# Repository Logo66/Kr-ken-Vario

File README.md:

# AURA-Kruecke

ESP32-S3-basiertes Variometer-Prototyping auf dem LilyGo T5 E-Paper S3 Pro.

## Hardware

- **Board:** LilyGo T5 E-Paper S3 Pro (ESP32-S3, 16 MB Flash, OPI PSRAM)
- **Sensoren (extern via I2C):** 2x BMP581, LSM6DSO32, BNO085, SHT40
- **Onboard:** BQ25896 Charger, BQ27220 Fuel Gauge, PCF85063 RTC, 4.7" E-Paper

## Setup

1. [PlatformIO](https://platformio.org/) installieren
2. `pio run` — kompiliert und zieht Dependencies
3. `pio run -t upload` — flasht auf das Board
4. `pio device monitor` — Serial Monitor @ 115200 Baud

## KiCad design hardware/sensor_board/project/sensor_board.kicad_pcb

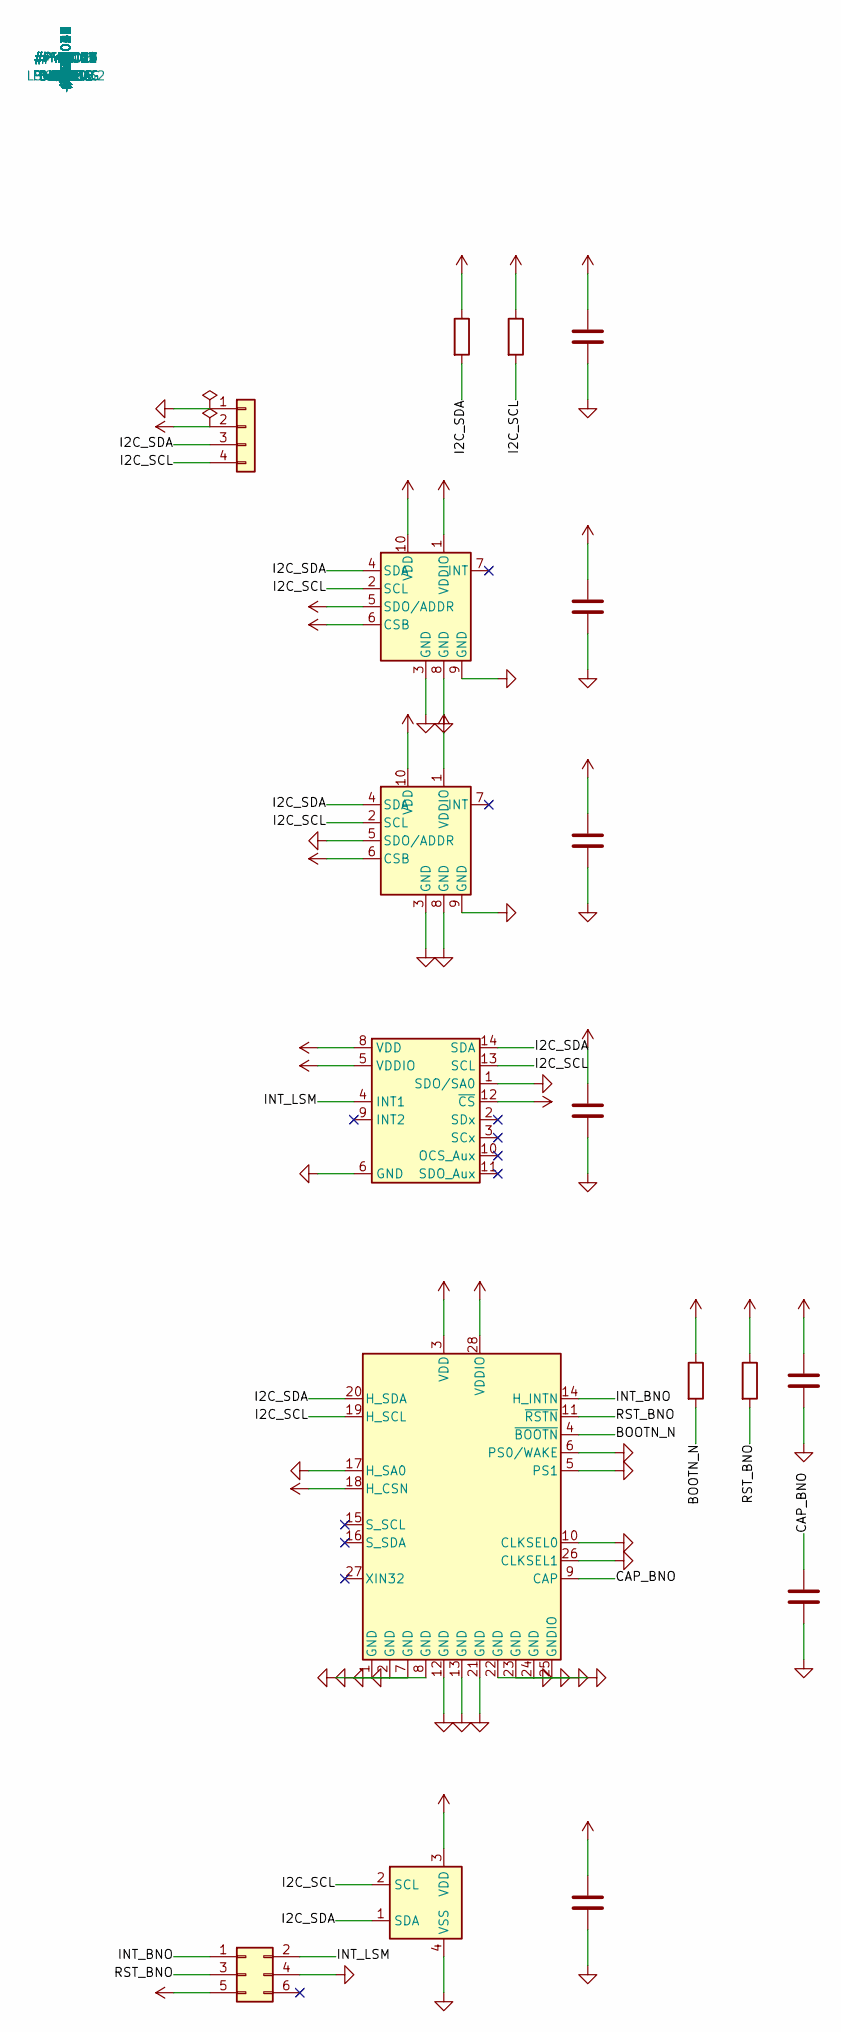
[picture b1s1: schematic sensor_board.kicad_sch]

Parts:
C1, C2, C3, C4, C5, C7: 100n; C_0402_1005Metric
C6: 10u; C_0805_2012Metric
J1: Qwiic; JST_SH_SM04B-SRSS-TB_1x04-1MP_P1.00mm_Horizontal
J2: INT_HDR; PinHeader_2x03_P1.27mm_Vertical
R1, R2: 4.7k; R_0402_1005Metric
R3, R4: 10k; R_0402_1005Metric
U1, U2: BMP581; BMP581_LGA-10_2x2mm
U3: LSM6DSO32; Bosch_LGA-14_3x2.5mm_P0.5mm
U4: BNO085; LGA-28_5.2x3.8mm_P0.5mm
U5: SHT40; Sensirion_DFN-4_1.5x1.5mm_P0.8mm_SHT4x_NoCentralPad

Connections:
+3V3: C1.1, C2.1, C3.1, C4.1, C5.1, C6.1, J1.2, J2.5, R1.1, R2.1, R3.1, R4.1, U1.1 (VDDIO), U1.5 (SDO/ADDR), U1.6 (CSB), U1.10 (VDD), U2.1 (VDDIO), U2.6 (CSB), U2.10 (VDD), U3.5 (VDDIO), U3.8 (VDD), U3.12 (~CS), U4.3 (VDD), U4.18 (H_CSN), U4.28 (VDDIO), U5.3 (VDD)
BOOTN_N: R3.2, U4.4 (~BOOTN)
CAP_BNO: C7.1, U4.9 (CAP)
GND: C1.2, C2.2, C3.2, C4.2, C5.2, C6.2, C7.2, J1.1, J1.MP, J2.4, U1.3 (GND), U1.8 (GND), U1.9 (GND), U2.3 (GND), U2.5 (SDO/ADDR), U2.8 (GND), U2.9 (GND), U3.1 (SDO/SA0), U3.6 (GND), U3.7 (GND), U4.1 (GND), U4.2 (GND), U4.5 (PS1), U4.6 (PS0/WAKE), U4.7 (GND), U4.8 (GND), U4.10 (CLKSEL0), U4.12 (GND), U4.13 (GND), U4.17 (H_SA0), U4.21 (GND), U4.22 (GND), U4.23 (GND), U4.24 (GND), U4.25 (GNDIO), U4.26 (CLKSEL1), U5.4 (VSS)
I2C_SCL: J1.4, R2.2, U1.2 (SCL), U2.2 (SCL), U3.13 (SCL), U4.19 (H_SCL), U5.2 (SCL)
I2C_SDA: J1.3, R1.2, U1.4 (SDA), U2.4 (SDA), U3.14 (SDA), U4.20 (H_SDA), U5.1 (SDA)
INT_BNO: J2.1, U4.14 (H_INTN)
INT_LSM: J2.2, U3.4 (INT1)
RST_BNO: J2.3, R4.2, U4.11 (~RSTN)

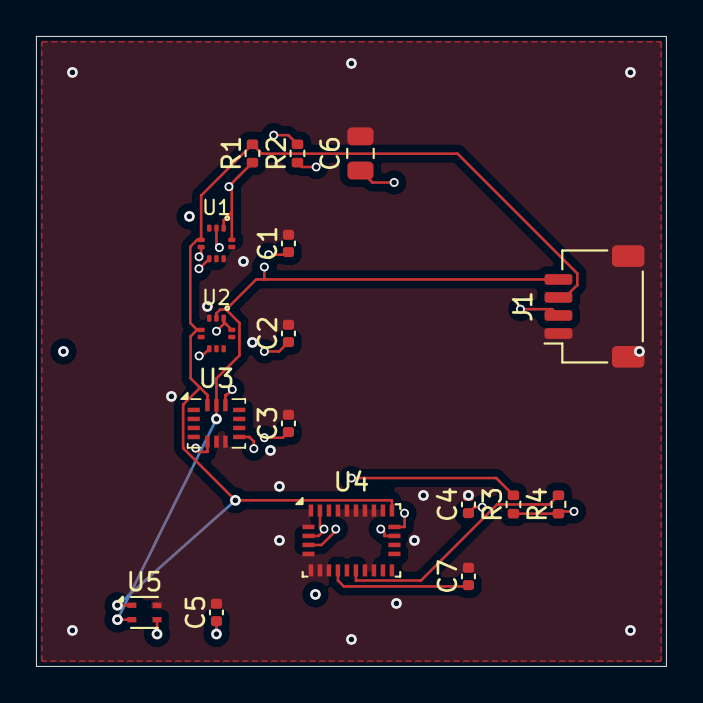
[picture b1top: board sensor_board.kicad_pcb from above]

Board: 4 copper layers, 35.0 x 35.0 mm, 17 parts (0 on the bottom side), 7 nets.

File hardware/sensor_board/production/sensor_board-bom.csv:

Designator,Quantity,Value,Footprint,MPN,Manufacturer,Description
"C1,C2,C3,C4,C5,C7",6,"100nF","C_0402_1005Metric","GRM155R71C104KA88D","Murata","MLCC 100nF 16V X7R 0402"
"C6",1,"10uF","C_0805_2012Metric","GRM21BR61A106ME51","Murata","MLCC 10uF 10V X5R 0805"
"R1,R2",2,"4.7kOhm","R_0402_1005Metric","RC0402FR-074K7L","Yageo","Chip Resistor 4.7k 1% 0402"
"R3,R4",2,"10kOhm","R_0402_1005Metric","RC0402FR-0710KL","Yageo","Chip Resistor 10k 1% 0402"
"U1,U2",2,"BMP581","BMP581_LGA-10_2x2mm","BMP581","Bosch Sensortec","Pressure Sensor LGA-10 2x2mm"
"U3",1,"LSM6DSO32","Bosch_LGA-14_3x2.5mm_P0.5mm","LSM6DSO32","STMicroelectronics","6-axis IMU Accel+Gyro LGA-14"
"U4",1,"BNO085","LGA-28_5.2x3.8mm_P0.5mm","BNO085","CEVA/Bosch","9-axis IMU SiP LGA-28"
"U5",1,"SHT40-AD1B","Sensirion_DFN-4_1.5x1.5mm_P0.8mm","SHT40-AD1B-R2","Sensirion","Temp/Humidity Sensor DFN-4"
"J1",1,"Qwiic","JST_SH_SM04B-SRSS-TB_1x04-1MP_P1.00mm","SM04B-SRSS-TB(LF)(SN)","JST","4-pin SMD Horizontal 1mm pitch"

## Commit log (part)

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2026-06-01 Analyse: burnair Stack- & Architektur-Benchmark fuer Flight Buddy KI
    Direkte Untersuchung (Asset-/Header-Inspektion, APK-Entpacken) in dieser
    Umgebung nicht moeglich: alle burnair.*-Hosts per Netz-Policy gesperrt
    (host_not_allowed), kein APK im Repo. Dokument haelt belegte oeffentliche
    Sekundaerquellen fest, kennzeichnet Vermutungen klar und liefert reproduzierbare
    Befehle zum Vervollstaendigen.
2026-06-02 Tooling: reproduzierbares burnair-Analyse-Skript + APK-Drop-Ordner
    Bereitet die vollstaendige A+B-Analyse vor, sobald die Voraussetzungen
    vorliegen (Netzzugang zu burnair.* und/oder APK unter ./burnair_apk/):
    - scripts/analyze_burnair.sh: Web-Assets/Engine/Bundler/Tiles/Header +
    APK-Framework-Marker/Libs/Hosts. Filtert Keys/Secrets/Query-Strings raus.
    - burnair_apk/README.md: definierter Ablageort fuer APKs.
    - .gitignore: *.apk und burnair_analyse_out/ ausgeschlossen.
2026-06-02 Tooling: .xapk-Unterstuetzung + Signaturpruefung im Analyse-Skript
    - Entpackt APKPure-.xapk-Buendel (base.apk + split-APKs) vor der Analyse
    - Signatur-Echtheitskontrolle via apksigner/keytool
    - .gitignore: *.xapk und *.obb ergaenzt
2026-06-02 Analyse: APK 3.0.57 verifiziert - nativer Kotlin-Stack + WebView-Karte
    Aufgabe B direkt am Artefakt (burnair Map 3.0.57, com.burnair.burnairmap)
    analysiert. Kernbefunde [APK]:
    - Native Android/Kotlin (kein lib/ -> kein Flutter/RN/Capacitor); klassische
    Views, kein Compose; KMP-Indiz (isHmppEnabled), Ktor.
    - Karte sehr wahrscheinlich WebView-gehostet (map.burnair.cloud): Geolocation
    + DOM-Storage + JS-Interface, LiveTracking-Callbacks; keine native Map-Lib,
2026-06-09 Analyse: Web-Stack verifiziert - Leaflet + Mapbox GL JS (nicht MapLibre)
    www.burnair.cloud-Startseite (per Upload) ausgewertet [WEB]:
    - Engine: Leaflet-Kern + Mapbox GL JS als Leaflet-Plugin (Vektor-Layer);
    fruehere MapLibre-Vermutung damit widerlegt.
    - Klassische jQuery-Multi-File-Seite, KEIN React/Vue/Vite/Next/Webpack
    (vite/next waren Substring-Fehltreffer).
    - Basiskarten: Google (GoogleMutant) + swisstopo WMTS + MapTiler; Mapbox-GL
2026-06-10 fix(fanet): TX-Tracking spec-konform + Live-TX gegated (Ticket D)
    Sicherheits-Funk: die Kruecke sendete im Flug spec-non-konforme Type-1-Frames
    (Hoehe >=2048m falsch wegen ueberschriebenem Scaling-Bit, Climb als Offset-128
    statt 2's-complement, Speed-Scaling ab >63km/h, Heading fehlte) -> falsche
    Position/Hoehe an fremde Piloten. Behoben:
    - Encoder neu gegen Autor-Spec (3s1d/fanet-stm32 protocol.txt): Alt bit0-10 +
    bit11 Scaling 4x, Speed bit7 Scaling 5x, Climb 7-bit 2's-complement, Heading
2026-06-10 feat(devices): Self-Registration + NVS-Token + Heartbeat, Bearer-Auth (Ticket C 1+2)
    Jedes Geraet bekommt eigene Identitaet statt geteiltem Master-Key:
    - POST /devices/register {mac, factory_secret, firmware_ver} -> eigener Device-Token,
    persistent in NVS (ueberlebt Neustart, kein Doppel-Register), + Pairing-Code.
    - Auth ueberall Authorization: Bearer <device-token> (X-Buddy-Key Legacy, nicht mehr genutzt).
    - POST /devices/heartbeat (Bearer) -> Server aktualisiert firmware_ver/last_seen (HTTP 200
    am Geraet verifiziert -> Server kennt Token).
2026-06-10 feat(map): standortbezogene CH-Karte — Bearer-Download + seek-per-Tile-Reader
    Echte Schweizer Karte (swissALTI3D) live auf dem Geraet:
    - map_pack.h: GET /maps/index + /maps/<region>/download mit Authorization: Bearer
    <device-token>, SHA-256-Verify gegen Manifest, atomar nach SD (Stufe 3, Ticket C).
    - pack_reader.h: parsePack neu als SEEK-PER-TILE (kein Full-Load) -> auch das 14.7 MB
    CH-Pack (2156 Tiles, 478k Konturen) passt. Laedt nur die Kacheln im Umkreis der
    Position (distanz-sortiert, gecappt). Byte-Format unveraendert (Vertrag gruen,
